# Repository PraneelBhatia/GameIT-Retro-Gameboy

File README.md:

----

# PCB Compact Gameboy

By: *Praneel Bhatia* & *Krishang Agarwal*

Date: 6 Jan 2024

----

## 1 Abstract

The Gameboy PCB project focuses on allowing the user to play games which can be run on an ATTiny85 Microcontroller along with other necessary components mentioned in this report. The games can be controlled by the user with the help of 3 push buttons: left button; right button; and Fire/reset button. These buttons and their functionality are chosen according to the programming of the games uploaded on the ATTiny85. The games will be displayed on an OLED display appropriately connected to the ATTiny85 chip. 

We duly made all the required connections on a breadboard to prototype the end product, which was successfully functioning after a number of trials and prototypes. A 9V power supply powered the breadboard prototype. A slide switch controlled the POWER ON and POWER OFF state of the prototype.

The end product would feature a compact Gameboy designed diligently on a suitable PCB design, powered by a provenly sufficient 3V button cell, overall allowing our product to be portable and used anywhere desired by the user.

This report will show all the steps taken to get to the end-product, all the challenges that we faced in the process and their respective solutions as well.

## 2 Introduction

The evolution of portable gaming has drastically shot up ever since the release of the first Gameboy by Nintendo in 1989, which set a profound standard for on the go gaming. When looking through the eyes of Practical Electronics, the endeavor to create a Gameboy serves as a comprehensive application of electronic principles and PCB fabrication, and aids us in developing the right skills needed for future projects in this field.

The functional purpose as well as the build complexity of this project has inspired us, as students, to bring this piece of technology to life, demonstrating the prowess that Practical Electronics can offer to one and reigniting the amusement that one receives from their childhood in their academic journey of adolescence. 

All components utilized in this project are deeply tied to circuit design and involve careful combination and connections of the electrical parts to ensure the correct working of the device. 

The idea of the working end-product can be simplified to its building blocks: An OLED Display where the games would be shown and the user will visualize their interaction with the same; Piezoelectric Buzzer to generate sounds from the game and corresponding actions; Push buttons for user input and control; Slide switch for power ON and OFF of the device; Power LED to signify ON or OFF state; Resistors to ensure electrical functionality; ATTiny85 Microcontroller chip; and lastly a 3V button cell to supply voltage to the device.

The implementation of the above mentioned parts along with their control with the help of a microcontroller is an engaging challenge which requires precision, trial and error, and perfection, all from which a plethora of experience has been gained. Combining and applying the skills learnt not only from this course, but many others from the past, i.e. Microcontrollers and Electrical Engineering. 

The rest of the report will duly focus on the required technicalities and further aspects of the making of our project.

## 3	Literature review

This project was inspired by the work of Yellow Purple<sup>[4]</sup>. 
Yellow Purple: https://www.youtube.com/@YellowPurple

The software or different games for the ATtiny85 was acquired from an open-source entity made by Andy Jackson<sup>[5]</sup>.
ATtiny85 Games: https://github.com/andyhighnumber/Attiny-Arduino-Games

Electrical formulas and methods were properly used thanks to the wonderful teaching and guidance of Professor Hartanto and Mr. Kremer.

## 4    Bill of Materials

| No. | Qty. | manufacturer                 | component         | ordering code (manufacturer) | vendor   | ordering code (vendor) | Price per unit €\* | Price €\* | Link                                                                                                                                    |
| --- | ---- | ---------------------------- | ----------------- | ---------------------------- | -------- | ---------------------- | ------------------ | --------- | --------------------------------------------------------------------------------------------------------------------------------------- |
| 1   | 1    | Microchip Technology         | ATTINY85-20PU     | ATTINY85-20PU                | Mouser   | 556-ATTINY85-20PU      | 1,54               | 1,54      | [Mouser](https://mou.sr/3FK7BNl)                                                                                                        |
| 2   | 1    | Joy-IT                       | OLED-Display      | SBC-OLED01                   | Reichelt | DEBO OLED2 0.96        | 7,99               | 7,99      | [Reichelt](https://www.reichelt.de/entwicklerboards-display-0-96-oled-display-ssd1306-debo-oled2-0-96-p266107.html?&trstct=pos_0&nbc=1) |
| 3   | 1    | TE Connectivity              | 8 DIP socket      | 1-2199298-2                  | Mouser   | 571-1-2199298-2        | 0,19               | 0,19      | [Mouser](https://mou.sr/3D2lK8w)                                                                                                        |
| 4   | 1    | Broadcom / Avago             | SMD orange LED (D1)   | HSMD-C150                    | Mouser   | 630-HSMD-C150          | 0,28               | 0,28      | [Mouser](https://mou.sr/3tH9zvz)                                                                                                        |
| 5   | 4    | Vishay / Draloric            | 1k SMD resistor (R1,R10,R9,R5)   | CRS1206QJW-102ELF            | Mouser   | 652-CRS1206QJW-102E    | 0,22               | 0,88      | [Mouser](https://mou.sr/470fv1l)                                                                                                        |
| 6   | 1    | ROHM Semiconductor           | 6.8k SMD resistor (R4) | SFR18EZPJ682                 | Mouser   | SFR18EZPJ682           | 0,15               | 0,15      | [Mouser](https://mou.sr/40xo8hl)                                                                                                        |
| 7   | 1    | Bourns                       | 300 SMD resistor (R2) | 652-CRS1206QFX-3003E         | Mouser   | 652-CRS1206QFX-3003E   | 0,3                | 0,3       | [Mouser](https://mou.sr/3surVPP)                                                                                                        |
| 8   | 1    | Renata                       | Battery Holder    | HU2032-LF                    | Mouser   | 614-HU2032-LF          | 2,05               | 2,05      | [Mouser](https://mou.sr/463qCFc)                                                                                                        |
| 9   | 1    | Panasonic Industrial Devices | Coin Cell Battery | CR-2032/HEN                  | Mouser   | 658-CR-2032/HEN        | 0,44               | 0,44      | [Mouser](https://mou.sr/48wTF5T)                                                                                                        |
| 10  | 3    | RUNCCI-YUN                   | Push Button       | B07WPBQXJ9                   | Amazon   | \------                | 0,28               | 6,99      | [Amazon](https://amzn.eu/d/bhxDwoe)                                                                                                     |
| 11  | 1    | Arduino                      | Arduino           | 782-ABX00087                 | Mouser   | 782-ABX00087           | 26,6               | 26,6      | [Mouser](https://mou.sr/3QmGRaR)                                                                                                        |
| 12  | 1    | EKULIT                       | Buzzer (SG1)         | AL-60SP05                    | Reichelt | SUMMER TDB 05          | 1,02               | 1,02      | [Reichelt](https://www.reichelt.com/pl/en/electromagnetic-buzzer-summer-tdb-05-p35918.html?r=1)                                         |
| 13  | 1    | APEM                      | Slide Switch            | 25336NA                    | Reichelt | UL 1054          | 3,10               | 3,10      | [Reichelt](https://www.reichelt.de/sg/en/slide-switch-angled-pitch-5-08-1-x-on-on-ss-25536-n-p105721.html?&trstct=pos_12&nbc=1)                                         |
| 14  | 1    | Panasonic                      | 10uf capacitor            | ECE-A1EN100UB                    | Mouser | 667-ECE-A1EN100UB          | 0,34               | 0,34      | [Mouser](https://www.reichelt.de/sg/en/slide-switch-angled-pitch-5-08-1-x-on-on-ss-25536-n-p105721.html?&trstct=pos_12&nbc=1)                                         |

The project initiated with the brainstorming of necessary features of the Gameboy and corresponding hardware and software to accommodate these features. The following had been initially considered along with their functionality:

1) OLED Display: A compact and effective display, with only 4 pins for simplicity, to display the games to the user.
2) Push Buttons: To enable the user to control and add input to the games (directional movements: left, right; actions: shoot, jump).
3) Piezoelectric Buzzer: Output sounds upon execution of certain actions by the user (e.g shoot out bullet) or events in the game (e.g: shoot down object).
4) Slide switch: To turn the device on or off.
5) Power LED: to signify whether the device is in the on or off state.
6) 3V Button Cell: supplying voltage to the circuit.
7) Resistors: for the correct and safe functioning of components and wiring of circuit.
8) Serial Peripheral Interface (SPI): Used to flash games onto the microcontroller using an ISP.
9) 9 DIP slot: enable interchanging of Attiny85 chips to run different games on the device as one attiny85 chip has only enough space for one game.
10) 6 DIP slot: to allow easy flashing of new games onto already mounted ATtiny85.
11) 4 DIP slot: to mount and elevate OLED to avoid physical interference with ATtiny85 mount. Also, to allow exchange of OLED screens as they are an expensive component. Directly soldering them onto the PCB will be a permanent mount and fail to pull them out of the circuit and reuse as easily.

## 5    PCB

### 5.1     Schematic
With all of the components in mind, we started preparing the schematic of the electrical connections that underlie our device. For this, we initially began our electrical sketch on Fusion 360, but later on moved it to Autodesk EAGLE because it was more comprehensive, common and interactive in the Practical Electronics course. 

Final Schematic:

 Figure 1: GameIT Schematic

At the top of the schematic, the ATtiny85, which is the chosen microcontroller for this project, can be seen. It has labels to depict connections to the buzzer, buttons and OLED display.

Right beneath, the buttons can be seen. They are connected to a 1k resistor to aid with proper functioning and indication of the input signal as 'high' when the button is pressed. Without the resistors, the input would 'float' and have an indeterminate value. The Fire button is also a RESET button, which therefore has a 6.8k resistor connected to it for noise immunity.[2]

Below the buttons are the connections for the power LED, power supply (coin cell battery CR2032), buzzer and OLED. 

Towards the right of the schematic, we have made the connections for the slide switch and connector pins with the appropriate connections to the ATtiny85 for flashing new games when needed. This makes the flashing of new games much easier for the user and helps the user in enjoying the device to the most.

### 5.2    PCB Design

After designing the schematic on Eagle, we clicked the "Generate/Switch to Board". This converted all the schematic symbols into part footprints. The next step was to design the PCB outline, the placement of the different parts and their connections, and the silk screen which accommodates all the labels and text on the PCB. Routing is the term used to describe the electrical connections of the parts on a PCB together.

#### 5.2.1 PCB Outline

We wanted our PCB outline to be similar to the silhouette of a game controller. This required a custom design which had to be made in Fusion 360 and then be imported to the dimension layer in Eagle. The outline in Fusion 360 was designed as any other normal sketch that would be done in a CAD software. Our base dimensions were 80mm x 70mm. All our dimensions as well as sketch can be seen in the picture below:

 Figure 2: PCB Dimension

This can be later imported into Eagle in the BRD viewer mode, where there is a panel on the extreme right edge dedicated to Fusion 360.

#### 5.2.2 Part placement

Once we had our desired board outline, we started to place the components on the board. The following is our layout:

Figure 3: Part Placement

- The movement buttons - Left and Right - are intuitively placed on the left and right panel of the board. 
- The fire button is placed right above the right button, hence allowing majority of right-handed players to easily access the fire button with their thumb, while still having control of the movement buttons.
- The Power LED is placed right beside the slide switch to turn ON the device which is on the top left corner of the device. 
- The OLED screen is in the middle, the ATtiny85 and its mount are placed right underneath, and then the flashing pins underneath that as well. 
- The Buzzer is above the Left button.
- The Battery Holder is above the Fire Button.

All the components were placed on the top side of the board for easy view, and were labeled properly on the silk screen for easy assembly for anyone else trying to recreate the project. The pins of the ATtiny85 chip were also labeled on the bottom of the board for easy referencing when needed.

The placement of all the components was smartly done to incorporate a compact, space efficient and aesthetic view.

#### 5.2.3 Routing

Now for the connections of all these parts, we went through a number of different ways till we got to the most fitting. To sum it all up, we incorporated the use of Top-layer connections, Bottom-layer connections, ground planes and placement of vias. Vias are used to connect the top and the bottom plane connections. We used a track width of 1 milimetre for the routings. For the vias, we used a drill of 0.5 and diameter of 1.5. All values in mm.

The tools we used for this task were the following: Net, Polygon, Rip-up, Rats Nest, and Via.

The first model of our connections was more explicit and intuitively done, as can be seen below:

Figure 4: First Routing

- From first sight, it can be seen that the connections were functionable, but not done in the best way. 
- The spacing of the connections could be improved.
- There were some connections that were not as efficient as they could be (e.g. the routes that some connections were taking; the unnecessary use of vias)
- There were some routings done at 90 degrees, which should be avoided.

We fixed this and made the routings much better after some attempts and produced our final routing for the PCB:

Figure 5: Final Routing

- It can be seen that the connections overall look much neater, with the space used up properly, and no distance wasted on routings. 
- There were no 90 degree routings.
- Top and Bottom plane routings were done properly so that there are not any unnecessary vias used.

Overall, our final model for the routing on the PCB focused on both aesthetic and functionally efficient connections. 

#### 5.2.4 Silk Screen

The Silk Screen is the layer on the PCB which has to be considered when giving the PCB in for industrial manufacturing. It consists of all the text and labels on the PCB to help yourself or someone else to assemble your PCB when needed or to simply add your label or any other necessary info on the PCB. 

1) Go to the "Text" tool and type in the desired text.
2) Place the text wherever you want.
3) Right click on the text and change the layer to "tPlace" for top silk screen or "bPlace" for bottom silk screen.

We placed values of resistors and labels to where each part is to be placed as easily understandable instructions for anyone else who wants to assemble our board from scratch. Additionally, we added our names and group number, as instructed, and our device name and inspiring quote to go along with it - GameIt "From breadboard to leaderboard".

### 5.3	Methodology 
In this section, we will talk about the process flow of the development of our end product, showing the beginning to end stages in its making. 

#### 5.3.1 Breadboarding

We begun bringing the product to life by modelling it on a breadboard first. We made use of jumper wires, an arduino power supply breakout board which made use of a 9V battery, and the rest of the components needed to form the device (i.e Buzzer, OLED, Buttons, Resistors, LED).

Following our schematic, we came up with the following breadboarded prototype:

Figure 6: Breadboard Prototype

This model worked perfectly, after which we went on to the PCB design stage.

#### 5.3.2 PCB Prototype

The PCB design process has already been discussed above. Our next step after prototyping was to implement our circuit on a real PCB. With the help of the tutors and Mr. Kremer, we were able to etch our first PCB in the chemical lab. 

We learnt about the different machines needed for the etching of the Copper plate, and the processes that go on to produce the end-product. 

**1) Printing the tracks on Dry Film**

The printer in the lab allowed us to printout our PCB connections on dry film. We first had the chance to view it as normally printed out to check if it was ok and then had it done on dry film. A major design feature is to mirror the bottom layer when printing as it will only be then when it would match the connections with the top layer. The print looked like this:

Figure 7: Paper printed tracks

Figure 8: Dry Film prints

The next step was to align the top and bottom layer prints of the dry film and tape them, leaving space to insert the copper board for the next step.

Figure 9: Aligned dry films

We now put the copper clad laminate (CCL) plate inside. We chose a CCL plate sized best for our PCB. We only had rectangular copper boards and further machined it down to suit our peculiar shape. Once the CCL plate was inside, we fed the assembly into a direct imaging machine, which used UV light to image the tracks onto the copper plates. We set it for 2.5 mins in the machine.

Figure 9: Copper plate inserted in dry film

**2) Developing**

The board was removed and then put into the Developer, where the developing solution (Sodium Chloride - NaOH) dissolves the photo-resist layer on the board. 

Figure 10: Developing Machine

**3) Etching** 

We then proceeded to the Etching stage. This is where all unwanted copper is removed from the copper plate and only the required circuit remains<sup>[6]</sup>. The copper which had its photo-resist layer removed in the developing solution in the developing stage was able to be dissolved by the etching liquid in the etching stage. The machine uses Ferric(III)-Chloride Hexahydrate to carry out this chemical process. In some cases, the liquid was foaming up above the machine edge and to prevent that, we moved the PCB from left to right to decrease the foam level. The PCB was attached to a clamp to ensure our safety and prevent contact with the chemicals.

Figure 11: Etching Machine

Figure 12: Rising foam levels during Etching

Figure 13: Etching end-product: Complete Circuit on CCL

Figure 14: Dried board from etching machine. "Top" is the top layer of the PCB and "Bottom" labels the bottom layer.

**4) Milling**

Now our PCB board with all routings done was finished. We wiped the board with alcohol after it was dried to clean it thoroughly and to ensure functionality. Our next step was to shape it into the desired shape. We took the help of Professor Muhs to do this. With the help of the drilling machine, holes were made to follow the desired profile. After that, a hand-saw was used to cut along the holes and get a rough outline. Finally, using sand-paper we sanded the rough edges and got it to be smoothened to a curve. Our PCB prototype was complete. We wiped it down once more with alcohol before proceeding with any further electrical processes to ensure functionality.

Figure 15: Drilling of holes into PCB

Figure 16: Sanding down the rough edges of the board.

The prototype PCB now had the desired shape that we intended. This profile allowed for a more ergonomic design which removed any sharp corners by sanding fillets to them, and to also provide a left and right holding platform for the users to have a better grip of the device and to use the buttons and device overall more intuitively. 

Figure 17: Milled and Sanded prototype PCB.

**5) Holes and Vias**

Drilling the holes for the vias and the THT (through hole technology) components was the next part of the process. We wiped the board down with alcohol to clean it and then went ahead to start the drilling. This was just for safety, but was not mandatory at this stage. 

For the drilling the holes, we used a PCB Drilling Machine - Variodrill<sup>[7]</sup>. The drill bit was chosen according to our via dimensions (1.5mm diameter, 0.5mm drill). We placed the board properly on the machines drilling platform. A magnifying glass helped us view the area to be drilled, and on pressing the pedal, the drill came up from the bottom and drilled through the PCB where positioned. We drilled holes for all the vias.

Figure 18: Drilling holes.

We wiped the board once again with alcohol to clean it before inserting in the vias, for proper functionality. This is important as all dust from drilling must be removed to ensure connectivity in the board. 

To choose the best sized via, we roughly placed a via on top of the holes they were supposed to go on and checked if their diameter suited our board or if it was interfering with the other tracks or connections where it was not supposed to. After soem trial and error in a size range, we picjed the vias with a 0.9mm drill and a 1.5mm diameter. This was sufficient for our board and corresponded with the availability in the lab.

Figure 19: Inserting Vias. **1**: Placing the via in the machine. **2**: Pressing the via into the board. 
**3**: Vias installed into the board.

We used the Continuity Test from the multimeter to check if all the connections existed. We went over all the vias, tracks and ground planes. Referring to the board layout and ciruit design on Eagle, we knew where to place the multimeter nodes to carry out this test. 

With the PCB etched and the vias installed, our prototype PCB was finally fully functionable, with all the necessary connections done and ready to be assembled.

**6) Soldering SMD and THT components**

The first step of the assembly was to solder the SMD (surface mounted device) components on the PCB and baking it in the oven.This was then followed by solderign the THT (through hole device) components on the board. These steps have been explained in detail in [Assembly](#63-assembly-process). 

Figure 20: SMD components, pointed with red arrows, soldered onto Prototype PCB. 

Figure 21: Functioning and assembled prototype

Our protoype was successfully completed and functional, after many troubleshootings done and problems solved, which will be talked about later in this report. 

**7) Industrial PCB**

The next step was to order an industrial PCB to take the device to the next stage. We troubleshooted our device, placed the silkscreen and did an ERC (electric rule check) and DRC (design rule check) check before ordering the board to place surity in the design. 

1) Download DRC file from the HSRW (Hochschule Rhein-Waal) Practical Electronics course moodle page. 

2) Upload the DRC file through the DRC check option in Eagle.

3) Fix the warnings shown.

Potential Warnings and Fixes:

**DRC**
- Warning - Wire Stubs\
-> Solution: Use rip-up tool to remove extra trace causing problem.

- Warning: Angle - When tracks are not made in an angle of 0, 45, 90 or 135<sup>[8]</sup>\
-> Solution: Remove and redo the traces at where this porblem is directed to. Use rip-up and net tools.

- Warning: Air wire - no/missed connection\
-> Solution: Make the connection using the net tool

**ERC**
- Warning - GND 'name'\
-> Solution: Approve it.

Once this was done and the PCB's were ordered, they arrived.

Figure 22: Industrial PCB

We then assembled, troubleshooted and finalized with these PCB's and got to our final product.

### 5.4 Assembly Process 

#### 5.4.1 Soldering SMD Components

Figure 23: SMD components placement

Before soldering the THT components we need to solder the SMD components marked with red arrows.

1) Place some solder paste on the places where the SMD components have to be placed.
2) Place the 4x 1K ohm Resistor, 1x 6.8k* ohm Resistor, 1x 300 ohm Resistor and one SMD LED
3) After this place it in the oven to let the solder melt and make a strong connection with the components
4) Once the solder has cooled down, check the conections using a multimeter

*If 6.8k Resistor doesn't work use a 4.7k Resistor

Figure 24: PCB going into oven
#### 5.4.2 Soldering THT Components

Figure 25: THT components placement

Now we can solder rest of the components onto the PCB

1) Solder the Switch, with the know faacing the edge
2) Solder the 3 push buttons on FIRE, LEFT and RIGHT labels
3) Solder the Buzzer keeping the +ve pin on +ve hole labled on the PCB
4) Solder the 8 pin DIP IC socket and place the ATTiny85 with the dot/Arrow facing towards the fire button
5) Solder the CR2032 Battery Holder and place a CR2032 Battery with +ve side facing up
6) Solder a female 4 pin header on top of the oled Screen and then plug in the OLED screen
7) If needed you can solder in female pin headers under the ATTiny 85 to flash games without having to remove the chip

if all done correctly, when turned on the LED should light up.Now power it off and proceed to next step

## 6   Programming and uploading games

### 6.1 Programming the Arduino Uno as an ISP and Burning BootLoader to Attiny85 (Modify)

An Arduino Uno Board is used to make a very simple ISP (In System Programmer) using, some male-to-male cables and 10uF capacitor.

Now follow these steps below:

1) To program the Uno use the Arduino IDE. Upload the ArduinoISP sketch from *File>Examples>11.ArduinoISP>ArduinoISP*, once the flashing is done unplug it from the computer. 
2) Take a group of 6 jumper leads and plug them from the Arduino Uno to the AtTiny85 according to the table below:

| Pin of UNO | Pin of AtTiny85 | Pins on GameIT PCB |
|---|--- | ---|
|5V  | pin 8 | VCC |
|GND | pin 4 | GND |
|D10 | pin 1 | PB5 |
|D11 | pin 5 | PB0 |
|D12 | pin 6 | PB1 |
|D13 | pin 7 | PB2 |

3) Now connect a 10uf 25v capacitor between GND and RESET pin of the Arduino UNO to prevent the arduino from resetting during the flashing process.

4) Plug the Arduino UNO to the computer. By default, the Arduino IDE does not support the ATTiny85 IC. If you do not have this support installed, it can be added by going to *File>Prefernces>Additional Boards Manger* URL's now paste [this](https://www.youtube.com/redirect?event=video_description&redir_token=QUFFLUhqbVlMbURQbDBRVEM0T3pxeVVvQjZpNGFUN3phZ3xBQ3Jtc0ttOXBKU0RqMERJQUhVZHMyS0FESkdVLVQ0VjllbDQxM2FjUUdEQkk1RHN1cXZrMjFPM3ctYXpHaXdvRU5HRzVycTM4VTVmSWR6X0ZjRDBnQWRCTUM3N05jc3YxWkIyRGdBNTRoNkJLMjNrYmVxZENOaw&q=http%3A%2F%2Fdrazzy.com%2Fpackage_drazzy.com_index.json&v=Y6YVJ5mxvxo)
 link in the field. Then go to *Tool>Board>Board Manager>ATTinyCore>Install*.

5) If you are using a brand new ATTiny85, it will probably need to have a bootloader installed. In this case, there isn't any actual bootloader code as such, but there are some 'fuse' settings which set certain things like processor speed and clock source.
    - Go to *Tools>Board>ATTinyCore>ATTiny25/45/85(NO BOOTLOADER)*
    - next select the chip *Tools>Chip>ATTiny85*
    - Next select the Clock source and speed *Tools>Clock Source (only set on bootload)>8 Mhz (internal)*
    - Select the right COM port *Tools>Port>COM#*
    - Now set the programmer as Arduino as isp (done above) *Tools>Programmer>Arduino as isp*
    - Now burn the bootloader onto the Attiny *Tools>Burn Bootloader* The programmer should flash for a few seconds, and you should see a message that theBootloader Burn was successful. At this point, you should be able to upload games onto the chip.

### 6.2  Uploading the games on the ATtiny85

1) Now download the codes from [Andy Jackson's](https://github.com/andyhighnumber/Attiny-Arduino-Games) github repository. We would recommend our favourite the [Space attack game](https://github.com/andyhighnumber/Attiny-Arduino-Games/tree/master/SpaceAttackAttiny) 
2) Downlaod and extract the folder then open it in the Arduino IDE and upload the *.ino* code. After successful flashing restart the Gameboy and the game should start working. 

The code for each game that can be flashed onto the ATtiny85 was programmed by [Andy Jackson](https://github.com/andyhighnumber/Attiny-Arduino-Games) from an opensource resource webboggles. Games included Space Attack, Tetris, Wren Rollercoaster, Bat Bonanza, Frogger, and many more. Some games require a different hardware and Clock setting see the ablove mentiond author's github page for more information.

We edited the home display which is shown when the game starts to show our names (Praneel and Krishang) along with the website of the opensource resource. 
It was done by editting the follwoing lines *202* and *203* of the Space attack game in the [SpaceAttackAttiny.ino](https://github.com/andyhighnumber/Attiny-Arduino-Games/tree/master/SpaceAttackAttiny) file:

```C++
    ssd1306_char_f6x8(0, 6, "PRANEEL BHATIA");  
    ssd1306_char_f6x8(0, 7, "KRISHANG AGARWAL");  
```
## 7 Troubleshooting and fixes

Although this should work as it is however we faced some issues in getting it to work, here are our problems and the solutions we found for them:

**(1)**\
**-Isuue:** The game appears to be working slow and lagging\
**-Fix:** We fixed this issue by reflashing the bootloader onto the AtTiny85 and making sure we select the 8 Mhz internal oscilator. After flashing the boot loader reupload the code and it should start normally 

**(2)**\
**-Isuue:** The fire button doesn't work\
**-Fix:** Although the game code mentions to use a 6.8k ohm and 1kohm voltage divider however in our case that didn't work we had to look over the ATtiny85 data sheet to see the threshold voltage at which the RESET is activated and adjusted the 6.8k ohm resitor to a 4.7K ohm resitor which made our fire button work again. We connected manually a 10k ohm resistor to the 6.8k ohm resistor in parallel by touching the wire-ends without soldering and realised it was working. We calculated the total resistance in parallel of the 6.8k and 10k resistor and then decided to just connect a resistor in series closest to this value - which was found out to be 4.05 - as standard resistance of 4.7k ohm.

**(3)**\
**-Issue:** The Attiny board URL isn't working\
**-Fix:** We used Arduino IDE 1.8.19(Windows Store 1.8.57.0) and it works. However it didn't work for us with newer version. Alternatively you can use another Attiny85 board package

**(4)**\
**-Issue:** The Breadboard prototype was not working\
**-Fix:** We used a multimeter to check for connectivity. There was a break in connectivity somewhere. The breadboard was faulty. We changed the breadboard and it worked.

**(5)**\
**-Issue:** Faulty OLED Schematic in Eagle - GND and VCC pins switched\
**-Fix:** right click on schematic symbol and edit device. Then name GND at correct pin. Disconnect all the pads and then connect the properly to ensure that the connections are done correctly in the .brd files as well.

**(6)**\
**-Issue:** Faulty Connection in PCB Prototype - VCC and GND switched for OLED\
**-Fix:** We manually used jumper wires to correct the connections. 

**(7)**\
**-Issue:** Ground planes not connected\
**-Fix:** Used jumper wires to manually connect isolated ground planes. Additionally, added vias to the next design to make ground planes connected.

**(8)**\
**-Issue:** Used isolated vias for ground plane connections\
**-Fix:** Did not name the vias "GND" to indicate that they had to be connected to the ground plane. Vias were hence isolated and no connection was done. To solve this, we manually scraped the silk screen from the company-ordered PCB and soldered the via to the exposed copper plate.

Figure 26: Connected Vias vs. Isolated vias.

**(9)**\
**-Issue:** Fire button not working\
**-Fix:** Faulty voltage divider circuit. Checked voltage range in datasheet of ATtiny85 for reset to be 0.3V ~ 0.9V. Our voltage measured was 0.254V. Increased the voltage by changing resistance: using a 4.7k resistor instead of a 6.8k one. Fire button was used properly now. Voltage measured now was around 1.2V, exceeding 0.9V and using the fire button.\

**(10)**\
**-Issue:** Missing ground plane\
**-Fix:** Scraped top ground plane, bent pin header and soldered it to top plane. Gave a neat look as it was covered by the OLED. Later, we edited the .brd file to ensure the ground plane was present.

Figure 27: Lack of ground plane for pad pointed by arrow
 
**(11)**\
**-Issue:** Connectivity break from via to pad\
**-Fix:** Soldered via to pad, hence re-establishing connection in trace.

Figure 28: Problem number pointing to its respective solution.

## 8	Result: Working GameBoy

## 9    Power Consumption and Battery Life

We calculated the power consumption and the consequent battery life of our device with the knowledge of the type of battery that we used and other values that we could get with the use of a multimeter. We used a bench power supply for this as well. 

Figure 29: Bench power supply

### Power Consumption

We have the following known Values using multimeter and Powersupply:

V<sub>supply</sub> = 3.3V (Measured)

I<sub>standby</sub> = 13.4mA (Measured)

I<sub>ingame</sub> = 17mA (Measured)

I<sub>avg</sub> = (I<sub>standby</sub> + I<sub>ingame</sub>) / 2 = 15.2mA 

\
Formula: P = I<sub>avg</sub>*V

Therefore power consumed = 3.3V * 15.2mA = 50.16mW

P<sub>consumed</sub> = 50.16mW

### Battery Life

We calculated the battery life by the following:

Formula: Battery Life = Battery Capacity(mAh)/Load Current(mAh)

Battery Capacity of CR2032 from datasheet<sup>[3]</sup>: 225mAh

Battery Life = 225mAh/13.5mA => 16.67 hours

## 10	Future Improvements

1) Add a cartridge system. SMD AtTiny85's will be loaded with different games to allow switching of different games easily using slot
2) Use an analog joystick with integrated push button to have a simple Joystick and screen to simplify the playing experience
3) Reduce the over all foot print so it can be fit into a wallet credit card space

## 11	References

[1] Minotti, M. (2018, December 12). 25 years of the Game Boy: A timeline of the systems, accessories, and games. VentureBeat. https://venturebeat.com/games/25-years-of-the-game-boy-a-timeline-of-the-systems-accessories-and-games/

[2] Community - Silicon Labs. Retrieved on 12.12.2023 from https://siliconlabs.my.site.com/community/s/article/pull-up-resistor-for-rst?language=en_US#:~:text=Answer-,The%20reset%20pin%20(%2FRST%20or%20RESETB)%20has%20an%20internal,or%20VIO%20on%20most%20devices).

[3] Panasonic. (2021, March). CR2032 Datasheet. Mouser. Retrieved January 8, 2024, from https://eu.mouser.com/datasheet/2/315/AAA4000C321-1137687.pdf

[4] Yellow Purple. (2022, March 7). DIY ATTiNy85 Mini Game Console PCB - Arcade Retro Multiple Games [Video]. YouTube. https://www.youtube.com/watch?v=Y6YVJ5mxvxo

[5] Andyhighnumber. (n.d.). GitHub - andyhighnumber/Attiny-Arduino-Games: Various games for the #Attiny Arcade and similar platforms. GitHub. https://github.com/andyhighnumber/Attiny-Arduino-Games

[6] ABL Circuits. (2023, June 12). PCB Etching 101. ABL Circuits. https://www.ablcircuits.co.uk/blog/blog-pcb-etching/

[7] Elektronik, B. (2023, February 7). Variodrill. Bungard Elektronik GmbH & Co.KG. https://www.bungard.de/en/machines/drilling/variodrill

[8] Description of errors in ERC / DRC. (n.d.). Element14 Community. https://community.element14.com/products/eagle/f/forum/41731/description-of-errors-in-erc-drc

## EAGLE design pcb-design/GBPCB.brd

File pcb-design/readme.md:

This is the folder where you save your pcb design with their related files. 

Please also submit a pdf / image version of your design

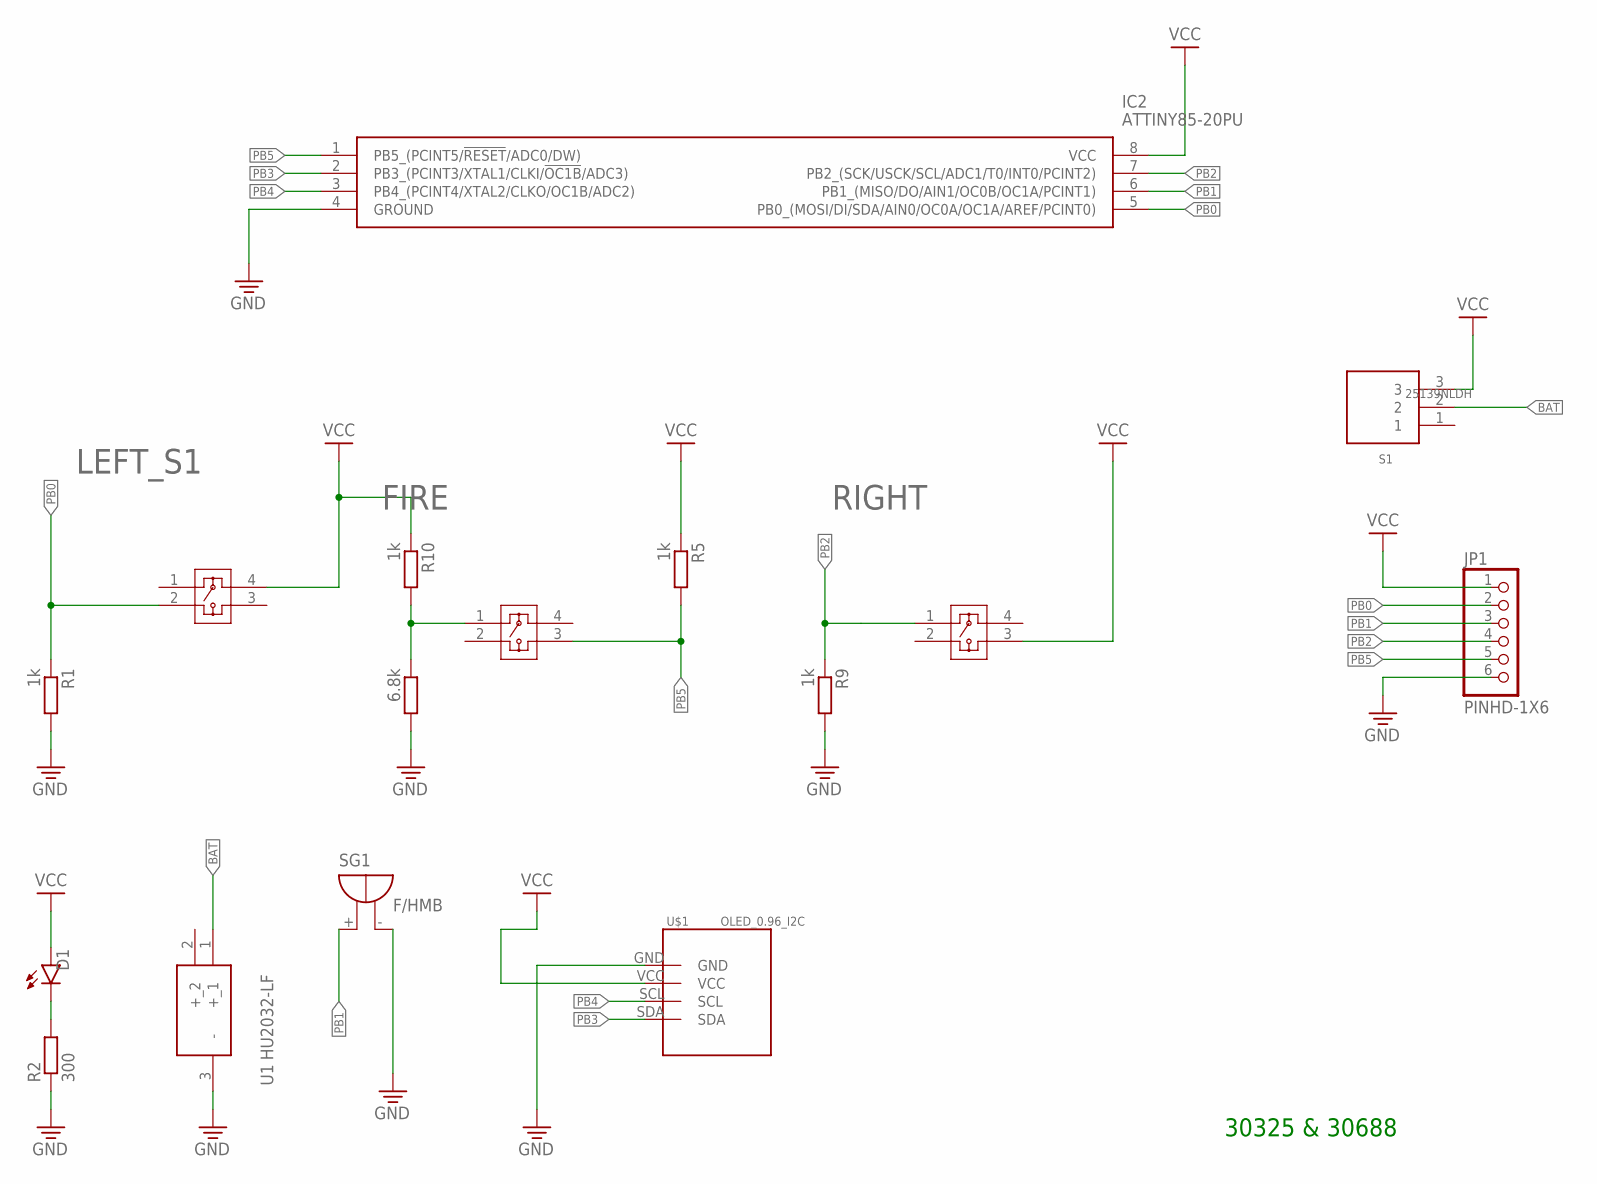
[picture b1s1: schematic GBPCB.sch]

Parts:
D1: LED_GREEN; CHIPLED_1206
FIRE: COM-10302COM-10302_SPK; COM-10302_SPK
IC2: ATTINY85-20PU; DIP781W56P254L950H533Q8N
JP1: PINHD-1X6; 1X06
LEFT_S1: COM-10302COM-10302_SPK; COM-10302_SPK
R1, R5, R9, R10: 1k; R1206
R2: 300; R1206
R4: 6.8k; R1206
RIGHT: COM-10302COM-10302_SPK; COM-10302_SPK
S1: 25139NLDH
SG1: F/HMB
U1: HU2032-LF; HU2032LF
U$1: OLED_0.96_I2C

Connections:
BAT: S1.2, U1.1 (+_1)
DGND: U$1.GND
GND: IC2.4 (GROUND), JP1.6, R1.2, R2.1, R4.2, R9.2, SG1.-, U1.3 (-)
unnamed: FIRE.1, R4.1, R10.2
unnamed: D1.C, R2.2
PB0: IC2.5 (PB0_(MOSI/DI/SDA/AIN0/OC0A/OC1A/AREF/PC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), JP1.2, LEFT_S1.2, R1.1
PB1: IC2.6 (PB1_(MISO/DO/AIN1/OC0B/OC1A/PCINT1)), JP1.3, SG1.+
PB2: IC2.7 (PB2_(SCK/USCK/SCL/ADC1/T0/INT0/PCINT2)), JP1.4, R9.1, RIGHT.1
PB3: IC2.2 (PB3_(PCINT3/XTAL1/CLKI/!OC1B!/ADC3)), U$1.SDA
PB4: IC2.3 (PB4_(PCINT4/XTAL2/CLKO/OC1B/ADC2)), U$1.SCL
PB5: FIRE.3, IC2.1 (PB5_(PCINT5/!RESET!/ADC0/DW)), JP1.5, R5.2
VCC: D1.A, IC2.8 (VCC), JP1.1, LEFT_S1.4, R5.1, R10.1, RIGHT.3, S1.3, U$1.VCC

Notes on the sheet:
30325 & 30688

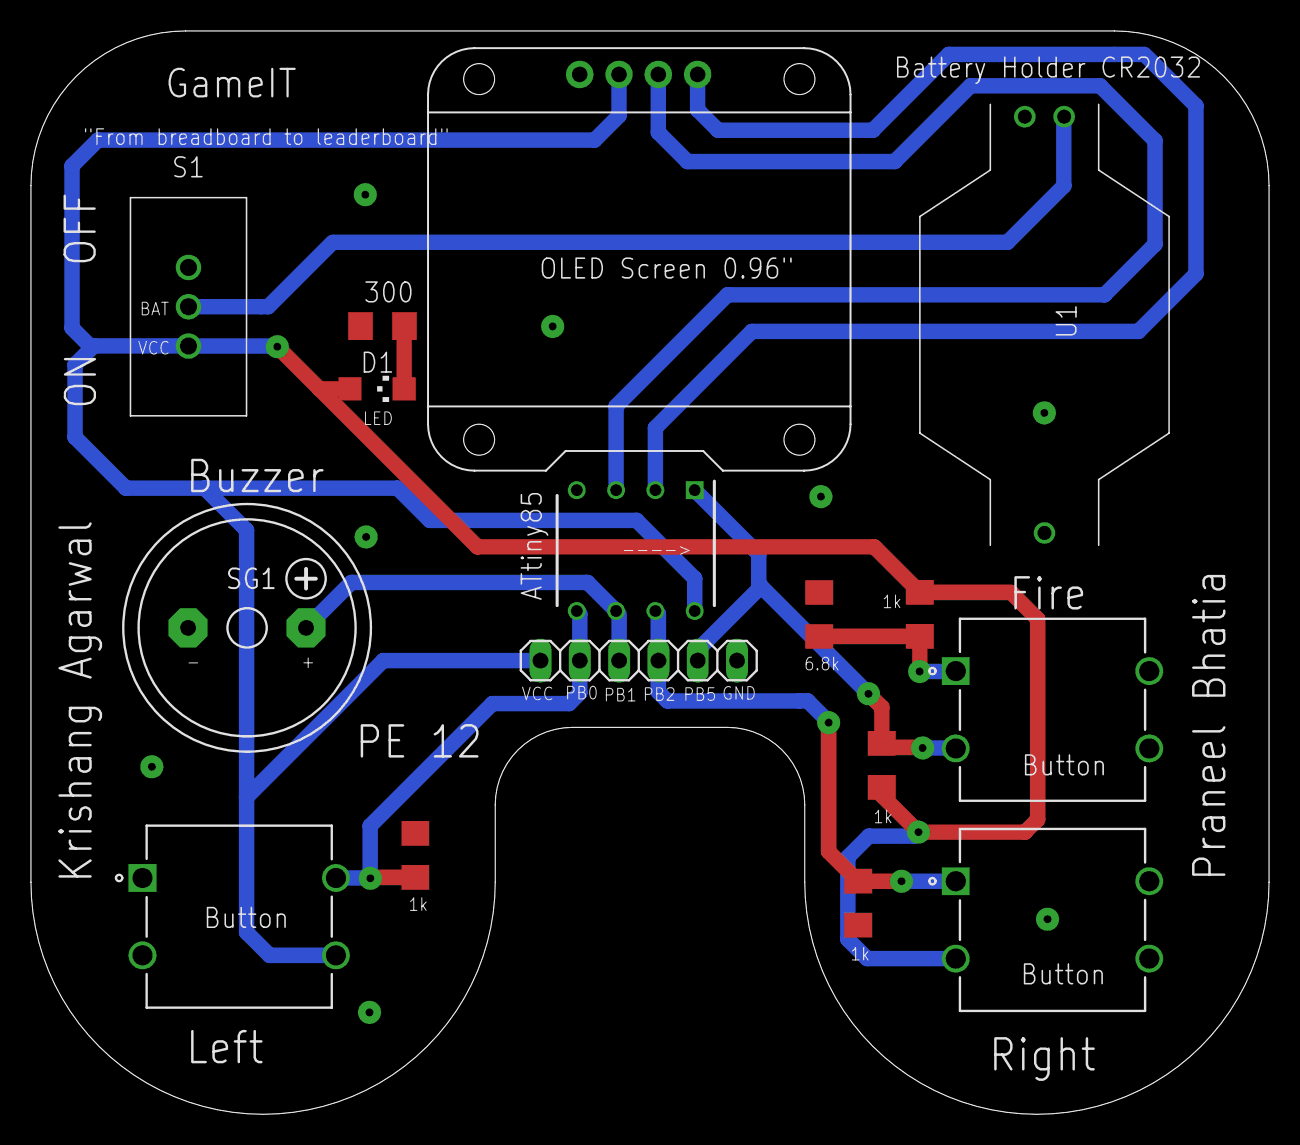
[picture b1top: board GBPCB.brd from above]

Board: 2 copper layers, 80.0 x 70.0 mm, 16 parts (0 on the bottom side), 11 nets.

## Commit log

2024-01-23 Upload
    Upload
2024-01-23 working video file
2024-01-23 Rename WorkingVideo.mp4 to img/WorkingVideo.mp4
2024-01-29 Add Video

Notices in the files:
parts and their libraries:
COPYRIGHT: Copyright (C) 2023 Ultra Librarian. All rights reserved.
